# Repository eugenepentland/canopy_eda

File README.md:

# Netlisp

*Schematics as S-expressions, written by an agent, compiled to KiCad.*

Netlisp is a command-line electronic design automation tool. A design is a
set of `.sexp` text files, not a drawing: you (or an agent) write the
schematic as S-expressions, and one binary evaluates it into a live web
viewer with electrical rule checks, a BOM, PCB placement and routing with
design-rule checks, Gerber and KiCad export, and design-review reports.
There is no GUI capture step; the browser is a viewer and review surface.

- **Language:** a small S-expression DSL with components, parameterised
  component families, modules with closures, nets inferred from pin
  connections, sections, assertions and formatting directives.
  See [docs/sexp-language.md](docs/sexp-language.md) and the generated
  reference [docs/language-forms.md](docs/language-forms.md).
- **Outputs:** HTML schematic with inline SVG, ERC and requirement checks,
  BOM resolution, PCB layout (placement, autorouting, copper pours, DRC),
  Gerber/drill fabrication packages, KiCad netlist + footprints + a full
  hierarchical `.kicad_sch` project, PDF reviews, thermal FEM cases.
- **Agent-first:** every operation is a structured CLI tool with a JSON
  schema (`netlisp tool list`), so an agent can drive the whole flow
  without a browser or a server.

Status: early public release.

- **Linux x86_64** is the supported platform: the test suite, the Guardian
  gate, CI and the maintainer's own server all run on it.
- **macOS (aarch64 and x86_64)** compiles but is untested. CI cross-compiles
  both targets on every push so the tree cannot regress into code that will
  not build there, and the HTTP server uses its kqueue backend; nothing has
  been run on a Mac yet.
- **Linux aarch64** is untested; only the toolchain archive is mirrored.
- **Windows** does not build (POSIX process groups in the subprocess layer,
  and the Guardian gate does not compile there either).

## Prerequisites

| Tool | Version | Needed for |
| --- | --- | --- |
| Zig | exactly the snapshot in [`.zigversion`](.zigversion) | everything; `scripts/install-zig.sh` installs it |
| Node.js | 20 or newer | build-time asset gates and JS unit tests run by `zig build` |
| Python | 3.11 or newer | two build-time policy checks (`tomllib`) |
| git | any recent | build-identity stamps and the Guardian gate |

Optional: `strip`/`readelf` (binutils) for release builds, Playwright for the
browser performance scripts, KiCad 8 for the board sync workflows, and
ElmerSolver for thermal comparisons. See
[ZIG_TOOLCHAIN.md](ZIG_TOOLCHAIN.md) for the full toolchain story.

## Quick start

```bash
git clone https://github.com/eugenepentland/netlisp.git
cd netlisp
scripts/install-zig.sh --link     # downloads and verifies the pinned Zig
zig build --seed=1                # first build fetches the Guardian gate once (network), ~2 min cold
zig build run -- serve --project-dir test/fixtures/stdlib-smoke
```

Open <http://127.0.0.1:7050>. The server binds loopback and treats local
requests as an admin, so nothing needs configuring for a laptop. The first
`zig build` downloads one dependency (the
[Guardian](https://github.com/eugenepentland/guardian-zig) code-quality gate,
pinned by URL and hash in `build.zig.zon`); every later build is offline.
Cold builds compile that gate at ReleaseSafe, warm rebuilds take seconds.

## Your first project

A project is a directory with `src/` holding designs and an optional `lib/`
holding your own components, footprints, pinouts and modules:

```text
my-board/
  src/
    my-board.sexp
  lib/            # optional; overrides the bundled library entry by entry
    components/
    footprints/
    modules/
```

Common passives (chip capacitors, resistors, inductors, ferrites and LEDs in
0201 to 0805 packages) come from the **bundled standard library**, so a
first design needs no library at all. Anything in your project's `lib/`
takes precedence over the bundled copy, `--lib-dir` (or `NETLISP_LIB_DIR`)
adds a shared library between the two, and `NETLISP_STDLIB_DIR` swaps the
bundled set for a directory of your own. The passive families need no
`(import …)`; test points, mounting holes and pin headers do. See
[docs/standard-library.md](docs/standard-library.md).

[`examples/blinky-breakout`](examples/blinky-breakout) is a complete board:
a 5 V input, a 3.3 V regulator, a Schmitt-trigger oscillator blinking an LED,
four spare gates on an expansion header, test points, mounting holes, and a
placed and routed two-layer PCB. Build it, check it, and hand it to KiCad:

```bash
zig build run -- build --project-dir examples/blinky-breakout blinky-breakout
zig build run -- check --project-dir examples/blinky-breakout blinky-breakout
zig build run -- export-kicad --project-dir examples/blinky-breakout \
    --output-dir ~/blinky-kicad --with-schematic blinky-breakout
```

[`examples/README.md`](examples/README.md) is the walkthrough: it goes from
that clone to a KiCad project, explaining every form as it appears, how the
bundled library and the project's own `lib/` resolve, how to drive the same
steps with `netlisp tool …`, and how the board was placed and routed.
[`test/fixtures/stdlib-smoke`](test/fixtures/stdlib-smoke) is the smaller
fixture next to it — a project with no `lib/` at all, proving the bundled
library end to end.

`netlisp help` lists every command; `netlisp reference [section]` prints the
language grammar from the binary itself.

## Driving it from an agent

Every structured operation is available locally with no server:

```bash
zig build run -- tool list
zig build run -- tool run_checks --project-dir my-board \
    --args '{"name":"my-board","profile":"preflight"}'
zig build run -- tool get_pcb_layout_image --project-dir my-board \
    --args '{"name":"my-board"}' --output my-board.png
```

Use `--args-file request.json` for larger requests. Text results go to
stdout; image tools return base64 JSON unless `--output` is given. The
tool schemas are the contract an agent should read first.

## Serving beyond localhost

Netlisp defaults to local hosting: it binds `127.0.0.1`, admits an unproxied
loopback request as admin, and refuses other requests. To keep a public
installation authenticated by Ward, set `NETLISP_AUTH=ward` and configure the
`WARD_*` URLs. The Ward client is bundled; local users need no auth server.

Alternatively, an authenticating reverse proxy can own auth with
`--allow-remote`, which makes **every** request netlisp receives an admin.
That flag cannot be combined with Ward mode. `--bind <addr>` controls the
listening interface. Configuration, systemd hosting, and KiCad sync tokens
are documented in [docs/auth.md](docs/auth.md).

## Building and testing

```bash
zig build --seed=1                       # Debug, self-hosted backend (default)
zig build --seed=1 -Doptimize=safe       # ReleaseSafe, still self-hosted, ~25 s
zig build --seed=1 -Doptimize=safe -Dllvm  # opt into LLVM codegen, minutes
zig build --seed=1 test                  # full suite plus the Guardian gate, ~5 min
zig build test-affected                  # only the tests your diff touches
zig build docs                           # regenerate docs/language-forms.md after a DSL change
```

`zig build` and `zig build test` fail when `docs/language-forms.md` is stale
or when Guardian finds a new violation; `guardian-check explain <check>`
says why. [docs/build-and-run.md](docs/build-and-run.md),
[docs/build-system.md](docs/build-system.md) and
[docs/testing-guide.md](docs/testing-guide.md) cover the build graph, test
filters, sharding and mutation tiers.

## KiCad round trips

The schematic is canonical; the board is updated to match. Declare
`(kicad-pcb "<path>")` in a design and use **Push to KiCad PCB** in the
schematic viewer (`POST /api/sync-kicad-pcb/:name`): the server diffs the
board against the flattened netlist and rewrites it in place, preserving
placements, pad nets and field values, with new instances staged per
section.

For the reverse direction, the design's **PCB Layout** page offers **Sync
from KiCad**, which previews mismatches and then imports the board's
placement, tracks, vias and outline as the design's starred layout. The
same import runs without a browser:

```bash
zig build run -- import-kicad-layout --project-dir my-board my-board
```

## Documentation

[docs/README.md](docs/README.md) is the index. The reference set:

- [docs/architecture.md](docs/architecture.md): what the tool does and how the pipeline fits together — start here
- [docs/sexp-language.md](docs/sexp-language.md): the design language, with [docs/language-forms.md](docs/language-forms.md) as the machine-checked reference
- [docs/standard-library.md](docs/standard-library.md): the bundled components and how overrides resolve
- [docs/agents.md](docs/agents.md): driving netlisp from an AI agent, and a `CLAUDE.md` for your own design repository
- [docs/webserver-api.md](docs/webserver-api.md): every HTTP route and structured tool
- [docs/auth.md](docs/auth.md): the local-only security model
- [docs/build-and-run.md](docs/build-and-run.md): the full build, run and deploy reference
- [ZIG_TOOLCHAIN.md](ZIG_TOOLCHAIN.md): the pinned compiler, mirrors and checksums

Working *on* netlisp: [CONTRIBUTING.md](CONTRIBUTING.md) first, then
[docs/worktrees.md](docs/worktrees.md), [docs/testing-guide.md](docs/testing-guide.md)
and [docs/build-system.md](docs/build-system.md).
[AGENTS.md](AGENTS.md) and [CLAUDE.md](CLAUDE.md) are the instruction files an
AI agent reads when it works in this repository — worktrees, the Guardian gate,
the spec ledger. Historical audits, plans and research notes live in
[docs/archive/](docs/archive), and describe nothing about how the tool behaves
today.

## Contributing

Pull requests are welcome. Read [CONTRIBUTING.md](CONTRIBUTING.md) first — two
things about this repository will otherwise surprise you: every `zig build`
runs a code-quality gate that has no bypass, and work happens on a branch in
its own worktree rather than in the `main` checkout. It also covers the
`SPEC.md` test-tag contract, the audit ledger, and what makes a bug report
about a misbehaving design actionable.

Participation is governed by our [Code of Conduct](CODE_OF_CONDUCT.md).
Security issues go through GitHub's private reporting, never a public issue —
see [SECURITY.md](SECURITY.md). Release notes live in
[CHANGELOG.md](CHANGELOG.md).

## License

[MIT](LICENSE) © 2026 Eugene Pentland. Vendored Zig packages under
`vendor/` and the browser libraries under `src/serve/assets/` keep their
own licenses. [THIRD_PARTY_NOTICES.md](THIRD_PARTY_NOTICES.md) lists every
one of them — component, version, license and where its text lives — and
flags the one copyleft component (the OpenCASCADE-based STEP importer,
LGPL-2.1 with the OCCT exception).

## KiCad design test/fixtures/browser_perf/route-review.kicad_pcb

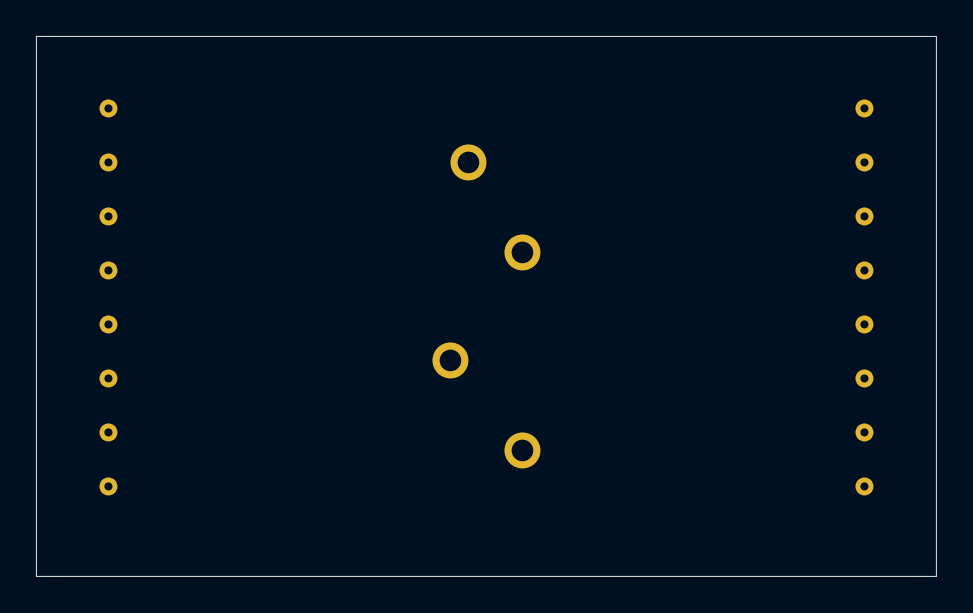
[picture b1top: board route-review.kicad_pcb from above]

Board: 2 copper layers, 50.0 x 30.0 mm, 20 parts (0 on the bottom side), 8 nets, no tracks yet.

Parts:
H1, H2, H3, H4: NPTH; MountingHole
J1: PERF_01_A; Terminal
J2: PERF_01_B; Terminal
J3: PERF_02_A; Terminal
J4: PERF_02_B; Terminal
J5: PERF_03_A; Terminal
J6: PERF_03_B; Terminal
J7: PERF_04_A; Terminal
J8: PERF_04_B; Terminal
J9: PERF_05_A; Terminal
J10: PERF_05_B; Terminal
J11: PERF_06_A; Terminal
J12: PERF_06_B; Terminal
J13: PERF_07_A; Terminal
J14: PERF_07_B; Terminal
J15: PERF_08_A; Terminal
J16: PERF_08_B; Terminal

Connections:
PERF_01: J1.1, J2.1
PERF_02: J3.1, J4.1
PERF_03: J5.1, J6.1
PERF_04: J7.1, J8.1
PERF_05: J9.1, J10.1
PERF_06: J11.1, J12.1
PERF_07: J13.1, J14.1
PERF_08: J15.1, J16.1
